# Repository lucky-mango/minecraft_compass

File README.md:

# Minecraft Compass — Digital Build

This repo documents my journey building a digital compass inspired by Minecraft, using an LED matrix PCB inside a custom 3D-printed enclosure.

## Preview

### FreeCAD design

### KiCAD design

## Repository Structure

| Path                         | Contents                                                                                                            |
| ---------------------------- | ------------------------------------------------------------------------------------------------------------------- |
| `STL/`                       | 3D-printable enclosure files. Subdirectories (`ver1`–`ver9`) track design iterations; the latest is in `STL/ver9/`. |
| `KiCAD/Clone-new_ledMatrix/` | Current KiCAD PCB project (schematic, layout, and Gerber exports).                                                  |
| `KiCAD/new_ledMatrix/`       | Earlier KiCAD project kept for reference.                                                                           |
| `FreeCAD/`                   | FreeCAD source models for the enclosure.                                                                            |
| `PCB/`                       | Fabrication-ready Gerber ZIP files for ordering the PCB.                                                            |
| `test_code/`                 | Firmware and animation test sketches.                                                                               |
| `datasheets/`                | Component datasheets (e.g. WS2812B-MINI LED).                                                                       |
| `images/`                    | Project screenshots and reference images.                                                                           |

## 3D Printing the Enclosure

The current STL files are in [`STL/ver9/`](STL/ver9/). Import them into your slicer (e.g. PrusaSlicer or Cura) and print as-is — no supports should be required.

## Prior Design Iterations

All previous versions of every file are preserved in Git history. Browse the [commit history](../../commits/main) on GitHub or run `git log` locally to find and restore any earlier iteration.

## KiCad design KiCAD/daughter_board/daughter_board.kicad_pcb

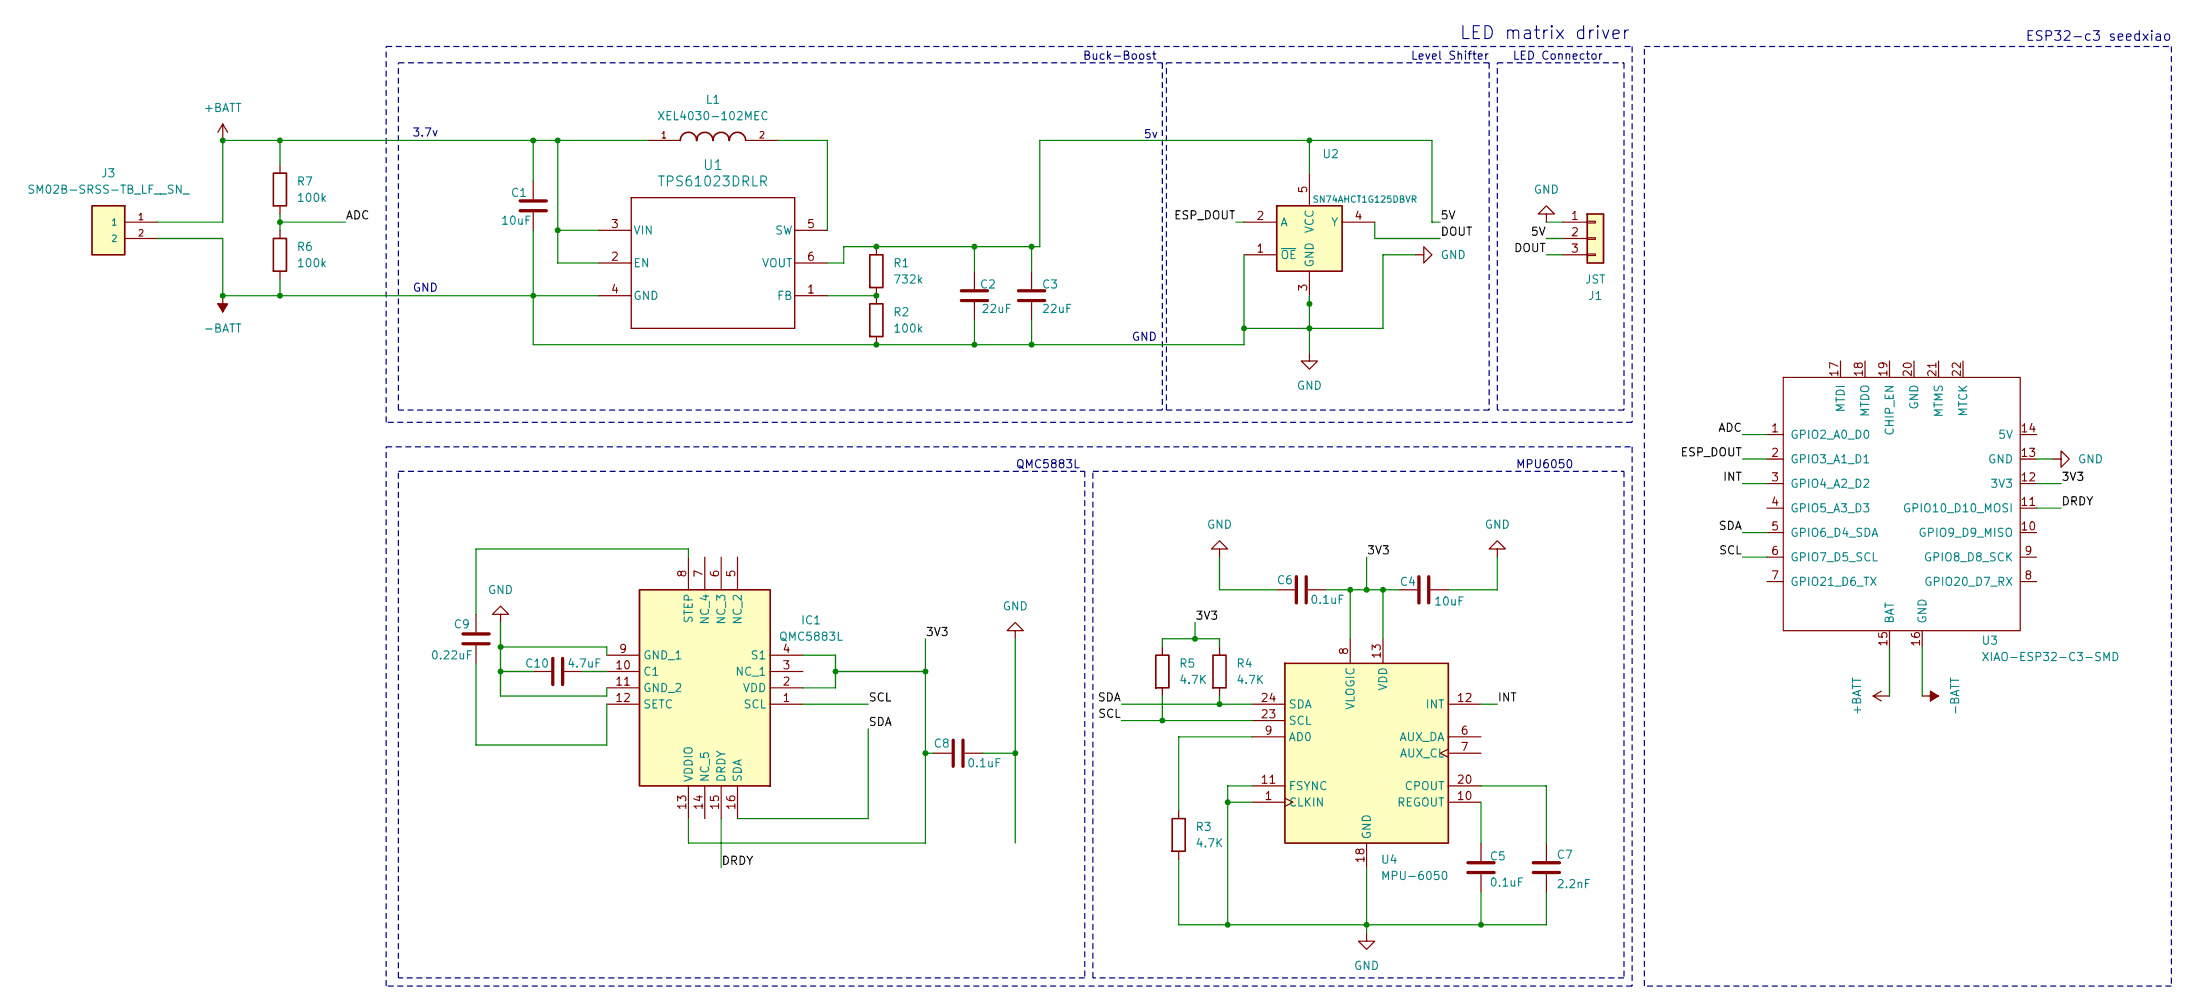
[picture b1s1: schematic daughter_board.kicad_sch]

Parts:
C1, C4: 10uF; C_0603_1608Metric; MPN 0603X106K160NT
C2, C3: 22uF; C_0603_1608Metric; MPN CL10A226MO7JZNC
C5, C6, C8: 0.1uF; C_0603_1608Metric
C7: 2.2nF; C_0603_1608Metric; MPN 0603B222K500NT
C9: 0.22uF; C_0603_1608Metric; MPN GRM155R71C224MA12D
C10: 4.7uF; C_0603_1608Metric; MPN CL10A475MA8NQNC
IC1: QMC5883L; MPN QMC5883L
J1: JST; JST_SH_SM03B-SRSS-TB_1x03-1MP_P1.00mm_Horizontal; MPN WT100EL-03-T-00
J3: SM02B-SRSS-TB_LF__SN_; MPN WT100EW-02-0-T-00
L1: XEL4030-102MEC; IND_XEL4030-102MEC; PARTREV 05/10/24
R1: 732k; R_0603_1608Metric; MPN RC0603FR-07732KL
R2, R6: 100k; R_0603_1608Metric; MPN CRCW0603100KFKEAC
R3, R4, R5: 4.7K; R_0603_1608Metric
R7: 100k; R_0603_1608Metric; MPN CRCW0603100KFKEAC.
U1: TPS61023DRLR; MPN TPS61023DRLR
U2: SN74AHCT1G125DBVR; SOT-23-5; MPN SN74AHCT1G125DBVR
U3: XIAO-ESP32-C3-SMD; XIAO-ESP32C3-SMD
U4: MPU-6050; InvenSense_QFN-24_4x4mm_P0.5mm_NoMask

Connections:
+BATT: C1.1, J3.1, L1.1, R7.1, U1.2 (EN), U1.3 (VIN), U3.15 (BAT)
-BATT: C1.2, C2.2, C3.2, C4.1, C5.2, C6.2, C7.2, C8.1, C10.2, IC1.9 (GND_1), IC1.11 (GND_2), J1.1, J3.2, R2.2, R3.2, R6.2, U1.4 (GND), U2.1 (~OE), U2.3 (GND), U3.13 (GND), U3.16 (GND), U4.1 (CLKIN), U4.11 (FSYNC), U4.18 (GND); also elsewhere on the board
/3V3: C4.2, C6.1, C8.2, IC1.2 (VDD), IC1.4 (S1), IC1.13 (VDDIO), R4.1, R5.1, U3.12 (3V3), U4.8 (VLOGIC), U4.13 (VDD)
/5V: C2.1, C3.1, J1.2, R1.1, U1.6 (VOUT), U2.5 (VCC)
/ADC: R6.1, R7.2, U3.1 (GPIO2_A0_D0)
/DOUT: J1.3, U2.4 (Y)
/DRDY: IC1.15 (DRDY), U3.11 (GPIO10_D10_MOSI)
/ESP_DOUT: U2.2 (A), U3.2 (GPIO3_A1_D1)
/INT: U3.3 (GPIO4_A2_D2), U4.12 (INT)
/SCL: IC1.1 (SCL), R5.2, U3.6 (GPIO7_D5_SCL), U4.23 (SCL)
/SDA: IC1.16 (SDA), R4.2, U3.5 (GPIO6_D4_SDA), U4.24 (SDA)
unnamed: C10.1, IC1.10 (C1)
unnamed: C9.1, IC1.12 (SETC)
unnamed: C9.2, IC1.8 (STEP)
unnamed: R1.2, R2.1, U1.1 (FB)
unnamed: L1.2, U1.5 (SW)
unnamed: R3.1, U4.9 (AD0)
unnamed: C7.1, U4.20 (CPOUT)
unnamed: C5.1, U4.10 (REGOUT)

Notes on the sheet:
QMC5883L
MPU6050
LED matrix driver
3.7v
GND
Buck-Boost
Level Shifter
LED Connector
GND
ESP32-c3 seedxiao

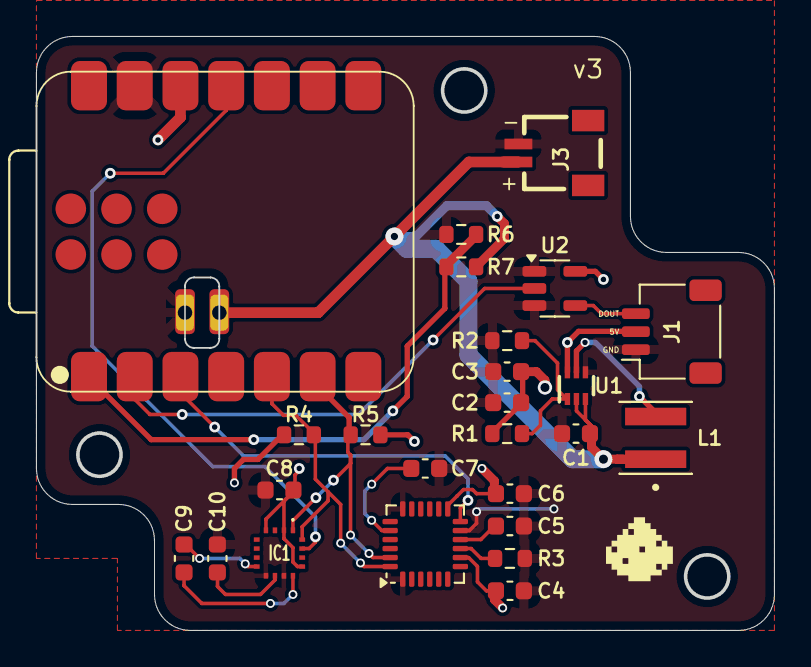
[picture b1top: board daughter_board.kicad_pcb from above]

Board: 2 copper layers, 40.9 x 32.9 mm, 26 parts (0 on the bottom side), 19 nets.

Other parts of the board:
0.8mm: Castellated_Hole_0.8mm

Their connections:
-BATT: 0.8mm.1; also elsewhere on the board

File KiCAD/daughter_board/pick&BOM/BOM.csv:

"Id";"Designator";"Footprint";"Quantity";"Designation";"Supplier and ref";
1;"U2";"SOT-23-5";1;"SN74AHCT1G125DBVR";;;
2;"U1";"TPS61023DRLR";1;"TPS61023DRLR";;;
3;"U3";"XIAO-ESP32C3-SMD";1;"XIAO-ESP32-C3-SMD";;;
4;"C6,C8,C5";"C_0603_1608Metric_Pad1.08x0.95mm_HandSolder";3;"0.1uF";;;
5;"R2,R7,R6";"R_0603_1608Metric_Pad0.98x0.95mm_HandSolder";3;"100k";;;
6;"0.8mm";"Castellated_Hole_0.8mm";1;"Castellated_Hole_0.8mm";;;
7;"C1,C4";"C_0603_1608Metric_Pad1.08x0.95mm_HandSolder";2;"10uF";;;
8;"J1";"JST_SH_SM03B-SRSS-TB_1x03-1MP_P1.00mm_Horizontal";1;"JST";;;
9;"C3,C2";"C_0603_1608Metric_Pad1.08x0.95mm_HandSolder";2;"22uF";;;
10;"R5,R3,R4";"R_0603_1608Metric_Pad0.98x0.95mm_HandSolder";3;"4.7K";;;
11;"C10";"C_0603_1608Metric_Pad1.08x0.95mm_HandSolder";1;"4.7uF";;;
12;"R1";"R_0603_1608Metric_Pad0.98x0.95mm_HandSolder";1;"732k";;;
13;"L1";"IND_XEL4030-102MEC";1;"XEL4030-102MEC";;;
14;"C9";"C_0603_1608Metric_Pad1.08x0.95mm_HandSolder";1;"0.22uF";;;
15;"U4";"InvenSense_QFN-24_4x4mm_P0.5mm_NoMask";1;"MPU-6050";;;
16;"J2";"JST_PH_S2B-PH-SM4-TB_1x02-1MP_P2.00mm_Horizontal";1;"S2B-PH-SM4-TB_LF__SN_2mm";;;
17;"IC1";"QMC5883L";1;"QMC5883L";;;
18;"";"";1;"";;;
19;"C7";"C_0603_1608Metric_Pad1.08x0.95mm_HandSolder";1;"2.2nF";;;

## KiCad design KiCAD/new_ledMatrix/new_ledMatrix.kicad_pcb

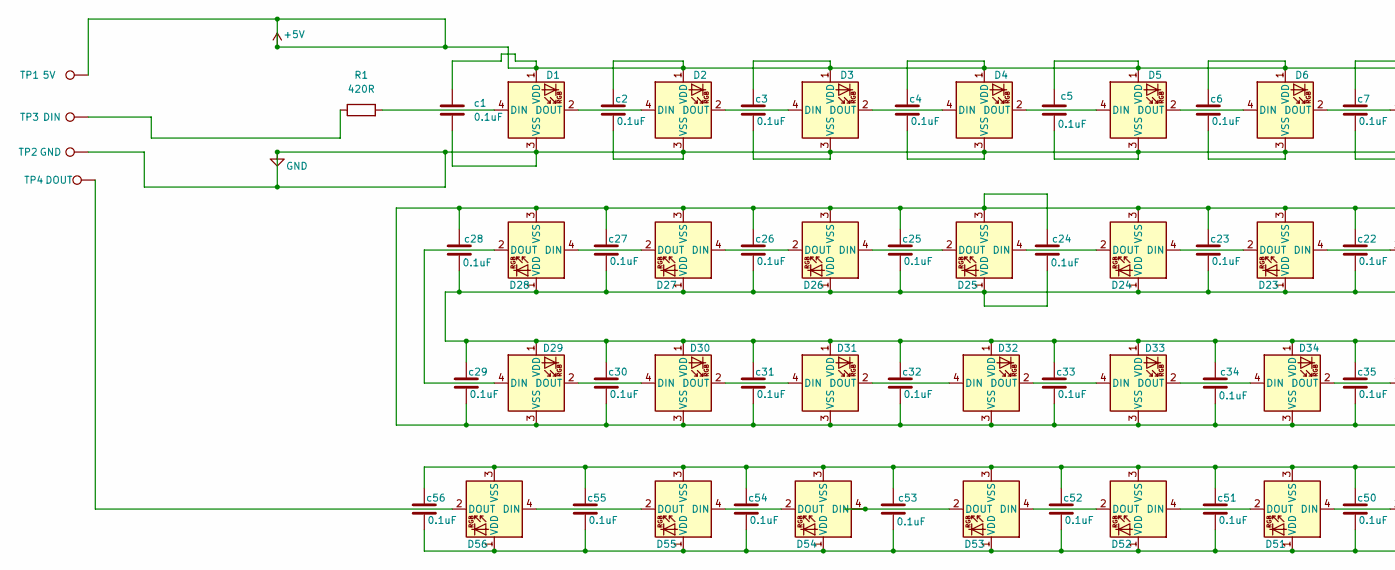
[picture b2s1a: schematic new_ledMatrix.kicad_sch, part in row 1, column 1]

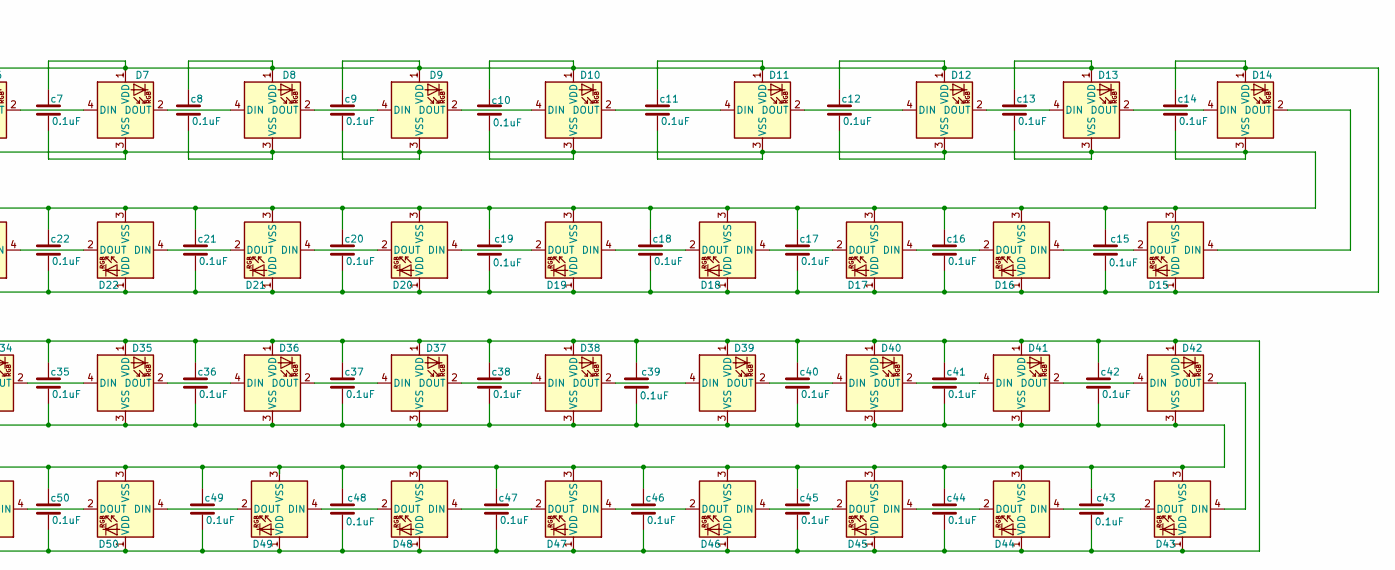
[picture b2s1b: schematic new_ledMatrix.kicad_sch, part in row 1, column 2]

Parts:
D1, D2, D3, D4, D5, D6, D7, D8, D9, D10, D11, D12, D13, D14, D15, D16, D17, D18, D19, D20, D21, D22, D23, D24, D25, D26, D27, D28, D29, D30, D31, D32, D33, D34, D35, D36, D37, D38, D39, D40, D41, D42, D43, D44, D45, D46, D47, D48, D49, D50, D51, D52, D53, D54, D55, D56: WS2812B-Mini; LED_SK6812MINI_PLCC4_3.5x3.5mm_P1.75mm
R1: 420R; R_1206_3216Metric
TP1: 5V; TestPoint_Pad_D2.5mm
TP2: GND; TestPoint_Pad_D2.5mm
TP3: DIN; TestPoint_Pad_D2.5mm
TP4: DOUT; TestPoint_Pad_D2.5mm
c1, c2, c3, c4, c5, c6, c7, c8, c9, c10, c11, c12, c13, c14, c15, c16, c17, c18, c19, c20, c21, c22, c23, c24, c25, c26, c27, c28, c29, c30, c31, c32, c33, c34, c35, c36, c37, c38, c39, c40, c41, c42, c43, c44, c45, c46, c47, c48, c49, c50, c51, c52, c53, c54, c55, c56: 0.1uF; C_0603_1608Metric

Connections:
unnamed: D1.4 (DIN), R1.2
unnamed: D1.2 (DOUT), D2.4 (DIN)
unnamed: D2.2 (DOUT), D3.4 (DIN)
unnamed: D3.2 (DOUT), D4.4 (DIN)
unnamed: D4.2 (DOUT), D5.4 (DIN)
unnamed: D5.2 (DOUT), D6.4 (DIN)
unnamed: D6.2 (DOUT), D7.4 (DIN)
unnamed: D7.2 (DOUT), D8.4 (DIN)
unnamed: D8.2 (DOUT), D9.4 (DIN)
unnamed: D9.2 (DOUT), D10.4 (DIN)
unnamed: D10.2 (DOUT), D11.4 (DIN)
unnamed: D11.2 (DOUT), D12.4 (DIN)
unnamed: D12.2 (DOUT), D13.4 (DIN)
unnamed: D13.2 (DOUT), D14.4 (DIN)
unnamed: D14.2 (DOUT), D15.4 (DIN)
unnamed: D15.2 (DOUT), D16.4 (DIN)
unnamed: D16.2 (DOUT), D17.4 (DIN)
unnamed: D17.2 (DOUT), D18.4 (DIN)
unnamed: D18.2 (DOUT), D19.4 (DIN)
unnamed: D19.2 (DOUT), D20.4 (DIN)
unnamed: D20.2 (DOUT), D21.4 (DIN)
unnamed: D21.2 (DOUT), D22.4 (DIN)
unnamed: D22.2 (DOUT), D23.4 (DIN)
unnamed: D23.2 (DOUT), D24.4 (DIN)
unnamed: D24.2 (DOUT), D25.4 (DIN)
unnamed: D25.2 (DOUT), D26.4 (DIN)
unnamed: D26.2 (DOUT), D27.4 (DIN)
unnamed: D27.2 (DOUT), D28.4 (DIN)
unnamed: D28.2 (DOUT), D29.4 (DIN)
unnamed: D29.2 (DOUT), D30.4 (DIN)
unnamed: D30.2 (DOUT), D31.4 (DIN)
unnamed: D31.2 (DOUT), D32.4 (DIN)
unnamed: D32.2 (DOUT), D33.4 (DIN)
unnamed: D33.2 (DOUT), D34.4 (DIN)
unnamed: D34.2 (DOUT), D35.4 (DIN)
unnamed: D35.2 (DOUT), D36.4 (DIN)
unnamed: D36.2 (DOUT), D37.4 (DIN)
unnamed: D37.2 (DOUT), D38.4 (DIN)
unnamed: D38.2 (DOUT), D39.4 (DIN)
unnamed: D39.2 (DOUT), D40.4 (DIN)
unnamed: D40.2 (DOUT), D41.4 (DIN)
unnamed: D41.2 (DOUT), D42.4 (DIN)
unnamed: D42.2 (DOUT), D43.4 (DIN)
unnamed: D43.2 (DOUT), D44.4 (DIN)
unnamed: D44.2 (DOUT), D45.4 (DIN)
unnamed: D45.2 (DOUT), D46.4 (DIN)
unnamed: D46.2 (DOUT), D47.4 (DIN)
unnamed: D47.2 (DOUT), D48.4 (DIN)
unnamed: D48.2 (DOUT), D49.4 (DIN)
unnamed: D49.2 (DOUT), D50.4 (DIN)
unnamed: D50.2 (DOUT), D51.4 (DIN)
unnamed: D51.2 (DOUT), D52.4 (DIN)
unnamed: D52.2 (DOUT), D53.4 (DIN)
unnamed: D53.2 (DOUT), D54.4 (DIN)
unnamed: D54.2 (DOUT), D55.4 (DIN)
unnamed: D55.2 (DOUT), D56.4 (DIN)
unnamed: D56.2 (DOUT), TP4.1
unnamed 57: R1.1, TP3.1; also elsewhere on the board

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
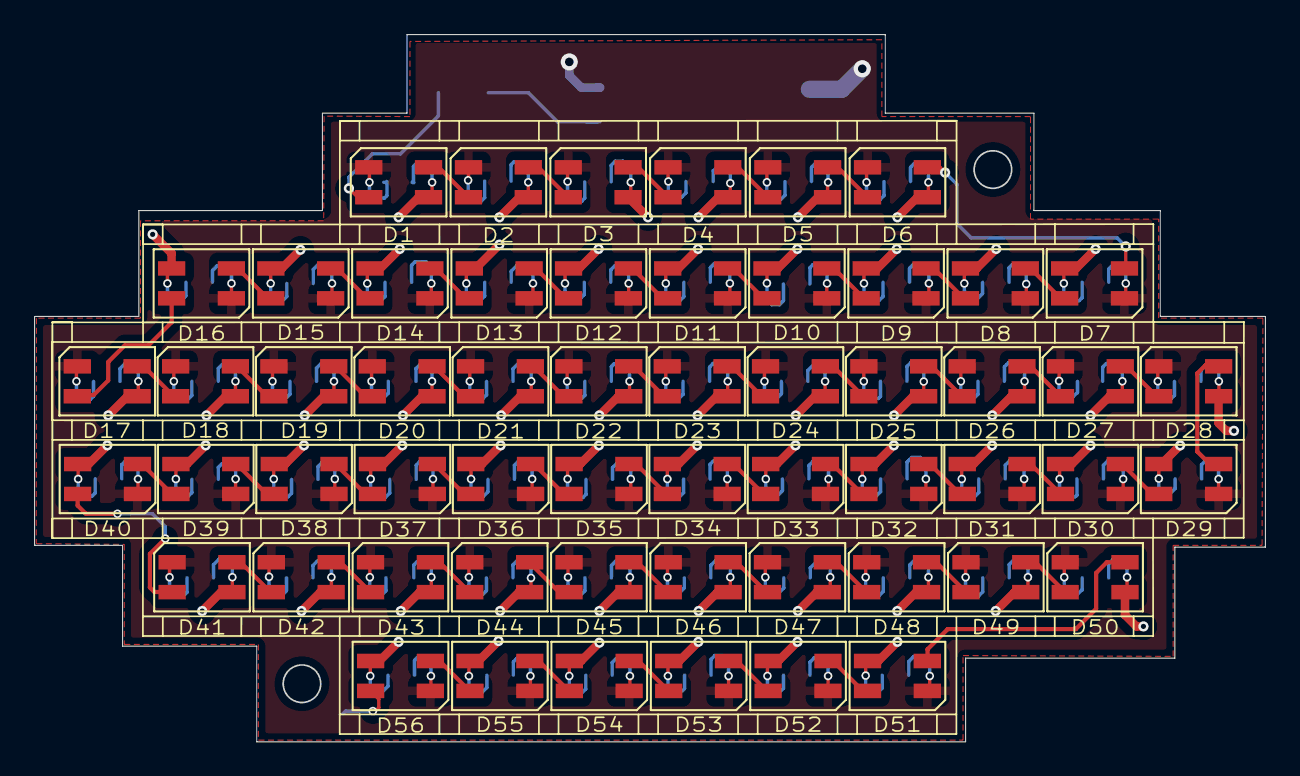
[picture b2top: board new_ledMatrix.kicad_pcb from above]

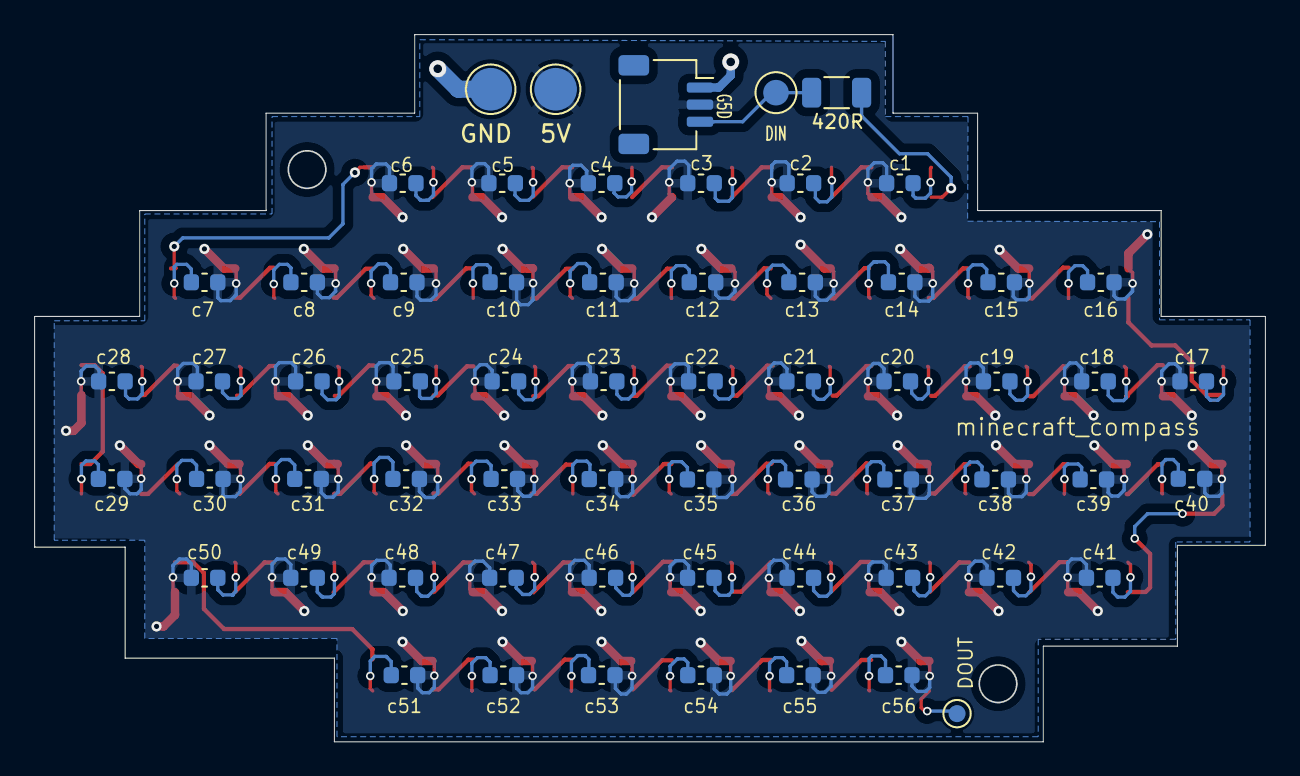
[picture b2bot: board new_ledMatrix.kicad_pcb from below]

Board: 2 copper layers, 72.0 x 41.3 mm, 118 parts (62 on the bottom side), 60 nets.

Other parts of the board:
G5D: JST_SH_SM03B-SRSS-TB_1x03-1MP_P1.00mm_Horizontal

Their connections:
unnamed 57: G5D.3; also elsewhere on the board

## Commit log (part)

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2025-09-14 ver_6
2025-09-14 Ver_6 top added
2025-09-25 added DOUT in PCB
2025-09-27 added DOUT to pcb
2025-09-29 via holes moved
2025-10-01 via holes alligned
2025-10-06 final silkscreen imporved with no drs error
2025-10-30 ver.8 of STL(Final)
2025-12-03 Initialize README with project details and images
    Added project overview and preview images.
2026-01-02 arbitrary update
2026-01-06 datasheets directory
2026-02-16 jst connector added
2026-03-17 extended grills for better led squarish lighting
2026-04-02 added funnels to the LED grid(space between each grid square is 0.1mm)
2026-04-26 added test-code dir and the frames
2026-05-03 added /indexed_pixels in root/images
2026-05-03 a duplicate image was found in indexedPixels, deleted the duplicate and fixed indexing
2026-05-06 Cleanup: keep single source STL/KiCad files; remove duplicates
2026-05-06 Initial plan
2026-05-06 Update README.md: remove versioned-file guidance, add structure table and print instructions
    Agent-Logs-Url: https://github.com/lucky-mango/minecraft_compass/sessions/5c0626f4-daf4-4494-bd9d-0f26a99ae4b4
2026-05-08 mag_led.ino and magnetometer.ino added in test_code/
2026-05-19 upadted pcb to ver7
2026-05-20 pcb hole placement fixed, also added it in freecad model view
2026-05-21 added skrew stand offs in free cad model for pcb in top plate
2026-05-21 exported stl files for the top and bottom plate
2026-05-27 in /FreeCAD changed the topPlate ecah pixel's bezzel: 0.1mm->0.2mm and screen thickness: 0.3mm -> 1.0mm, also exported both models as stl in /3dmodels/compass_case
2026-05-29 3d model top plate pcb screw hole 5H->6H
2026-06-08 skrew hole in top plate -tolerance increased
2026-06-11 custom clearance on the bottom_plate for mpu6050 and hmc58833L skrew holes
2026-06-16 added daughter a daughterbaord in /Kicad and create the buck boost converter schematic only
2026-06-17 in /Kicad/daughterboard added the mpu6050 schematic in the daughter board
2026-06-18 added datasheets, 3d models and alsocreated the schematic for qmc5883L
2026-06-18 kicad schematic finished for the daughter board (initial design)
2026-06-18 added power connector to the schematic, next step is to make the footprint
2026-06-21 completed new freecad base_plate and the KiCAD pcb design
2026-06-21 added a new stl file for base_plate for m2x2mm heat inserts
2026-06-23 in /FreeCAD model added skrews and the final daughter board,also in /Kicad added voletage divider in daughter board
2026-06-23 in /KiCAD changed the silkscreen from actual values to reference notations
2026-06-25 clean ip in /KiCAD of old gerber .zip files
2026-06-28 in /FreeCAD added the deposed c.s. also added the stl file for the same in /3dModels
